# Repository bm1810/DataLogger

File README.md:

# DataLogger
Development files for DataLogger project

-- SCRIPTS --
Development scripts can be accessed in the scripts folder. These should be uploaded to the Arduino to which the datalogger shield is connected

-- EAGLE --
The Eagle folder holds the Eagle cad files and drawing files to route the boards on an S63 milling machine.

-- BOXCAD --

This folder holds the 3D printer STL files and Solidworks CAD files from creation of the box.

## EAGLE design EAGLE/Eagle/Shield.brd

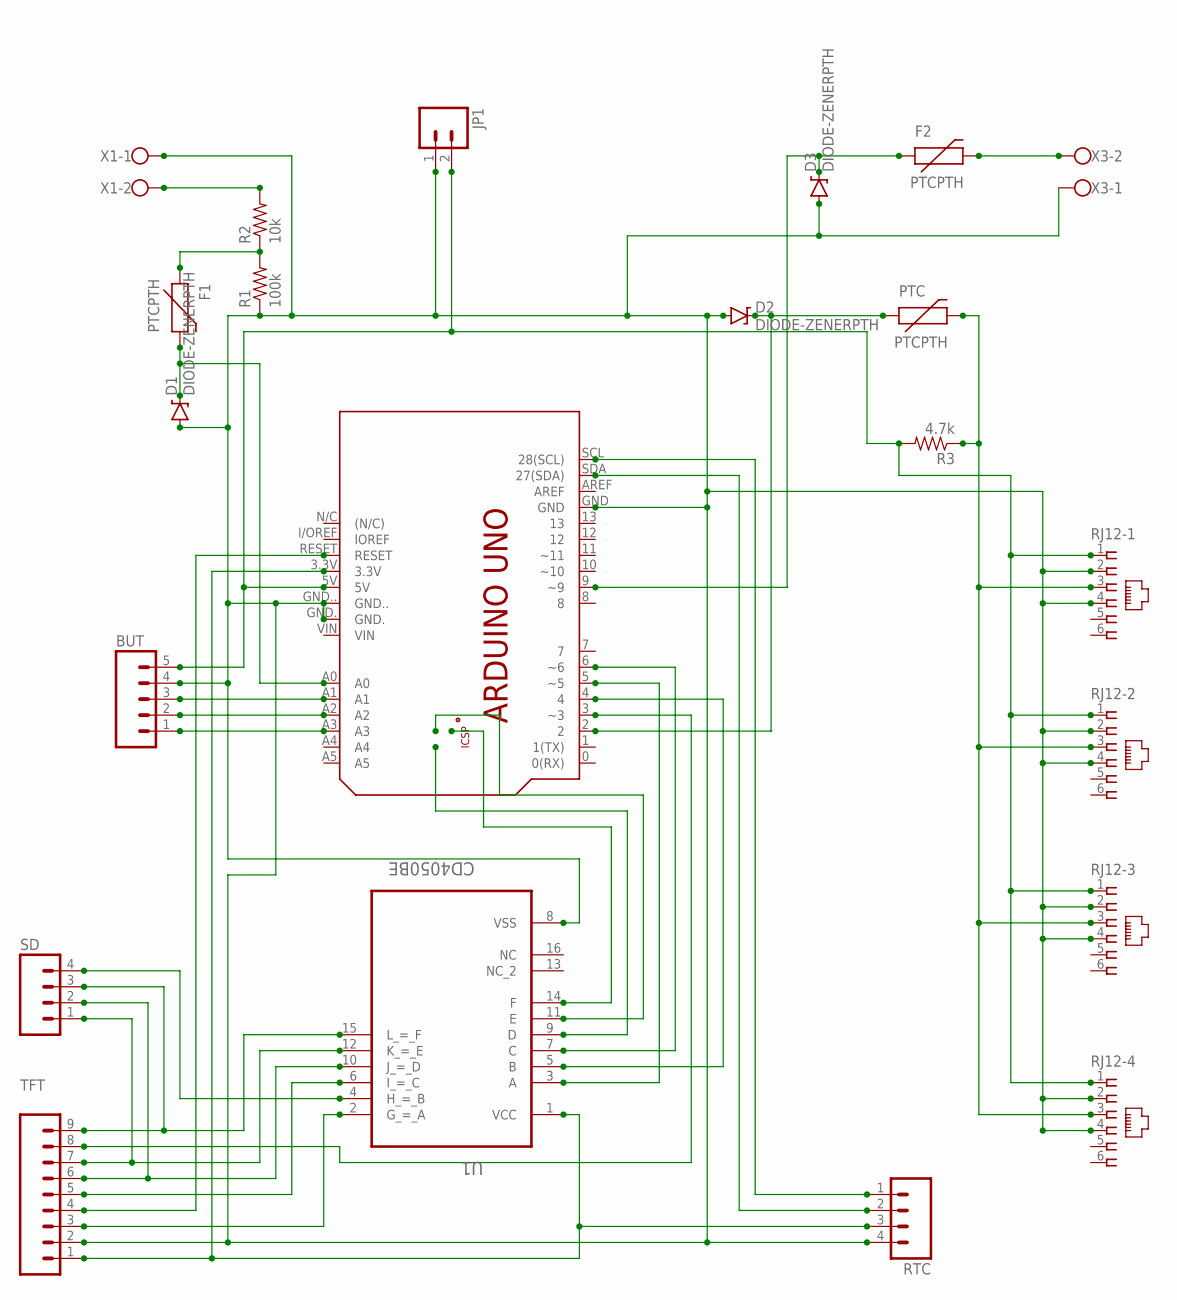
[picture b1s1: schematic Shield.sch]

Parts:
BUT: M05PTH_LONGPADS; 1X05_LONGPADS
D1, D2, D3: DIODE-ZENERPTH; DIODE-ZENER
F1, F2: PTCPTH; PTC
JP1: M023.5MM; SCREWTERMINAL-3.5MM-2
PCB1: ARDUINO_UNO
PTC: PTCPTH; PTC
R1: 100k; AXIAL-0.3
R2: 10k; AXIAL-0.3
R3: 4.7k; AXIAL-0.3
RJ12-1, RJ12-2, RJ12-3, RJ12-4: 555165-1
RTC: M04LONGPADS; 1X04_LONGPADS
SD: M04LONGPADS; 1X04_LONGPADS
TFT: M09LONGPADS; 1X09_LONGPADS
U1: CD4050BE; DIP254P762X508-16
X1, X3: W237-102

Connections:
GND: BUT.4, D1.P$2 (A), D2.P$2 (A), D3.P$2 (A), JP1.1, PCB1.GND, PCB1.GND., PCB1.GND.., R1.P$1 (1), RJ12-1.2, RJ12-1.4, RJ12-2.2, RJ12-2.4, RJ12-3.2, RJ12-3.4, RJ12-4.2, RJ12-4.4, RTC.4, TFT.2, U1.8 (VSS), X1.1, X3.1
unnamed: BUT.3, PCB1.A1
unnamed: PTC.P$2 (2), R3.P$1 (1), RJ12-1.3, RJ12-2.3, RJ12-3.3, RJ12-4.3
unnamed: PCB1.3.3V, RTC.3, TFT.1, U1.1 (VCC)
unnamed: D2.P$1 (C), PCB1.2, PTC.P$1 (1)
unnamed: PCB1.RESET, TFT.4
unnamed: SD.4, U1.4 (H_=_B)
unnamed: PCB1.5 (~5), U1.3 (A)
unnamed: PCB1.6 (~6), U1.7 (C)
unnamed: PCB1.MOSI, U1.9 (D)
unnamed: TFT.3, U1.2 (G_=_A)
unnamed: TFT.5, U1.6 (I_=_C)
unnamed: SD.2, TFT.6, U1.10 (J_=_D)
unnamed: PCB1.3 (~3), TFT.8
unnamed: SD.1, TFT.7, U1.12 (K_=_E)
unnamed: SD.3, TFT.9, U1.15 (L_=_F)
unnamed: PCB1.SCK, U1.11 (E)
unnamed: PCB1.MISO, U1.14 (F)
unnamed: BUT.5, JP1.2, PCB1.5V, R3.P$2 (2), RJ12-1.1, RJ12-2.1, RJ12-3.1, RJ12-4.1
unnamed: BUT.2, PCB1.A2
unnamed: PCB1.4, U1.5 (B)
unnamed: BUT.1, PCB1.A3
unnamed: PCB1.SDA (27(SDA)), RTC.2
unnamed: PCB1.SCL (28(SCL)), RTC.1
unnamed: F1.P$1 (1), R1.P$2 (2), R2.P$1 (1)
unnamed: D1.P$1 (C), F1.P$2 (2), PCB1.A0
unnamed: R2.P$2 (2), X1.2
unnamed: F2.P$2 (2), X3.2
unnamed: D3.P$1 (C), F2.P$1 (1), PCB1.9 (~9)

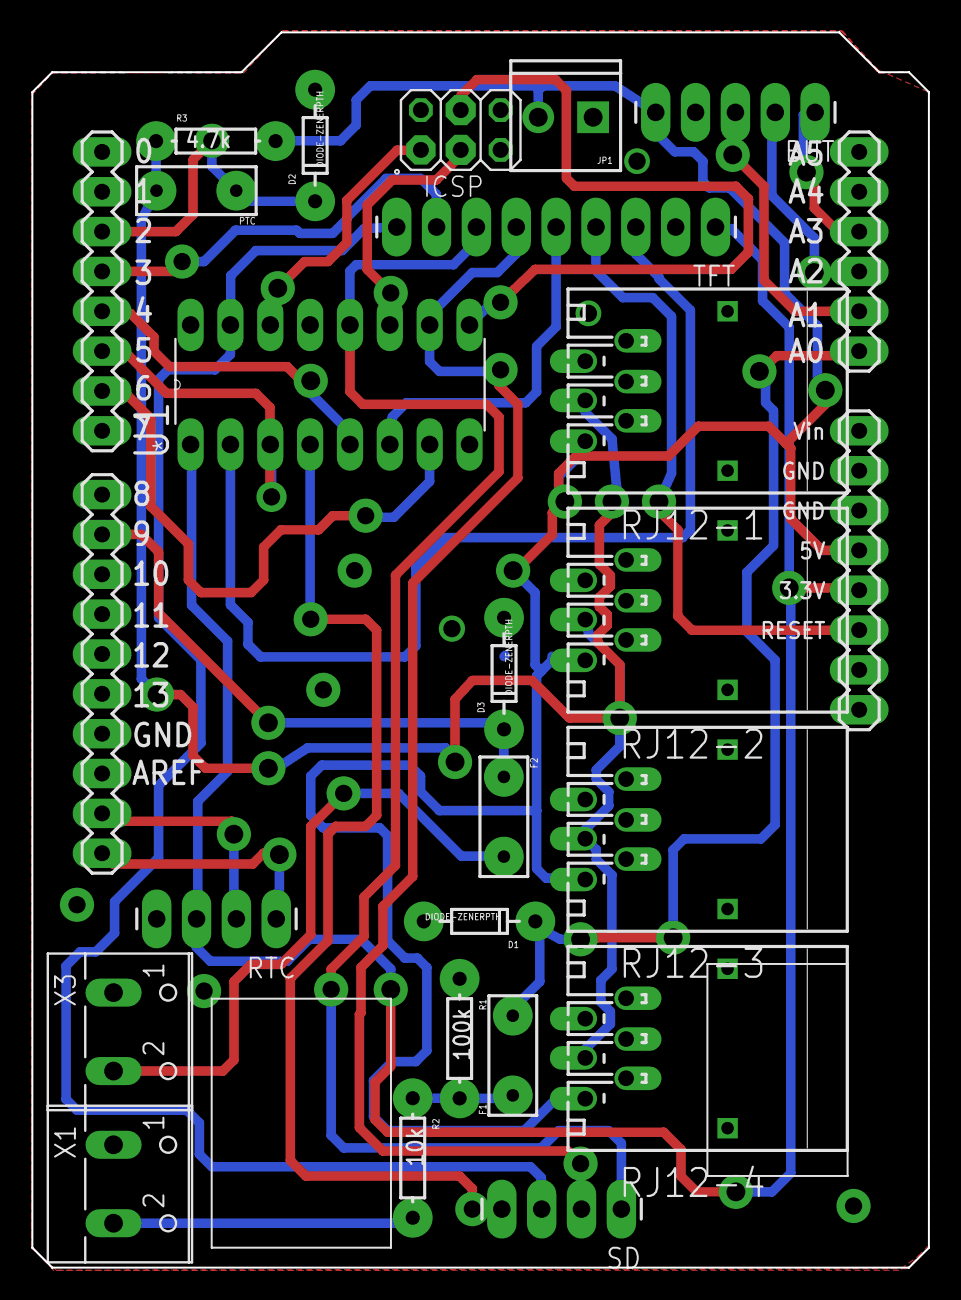
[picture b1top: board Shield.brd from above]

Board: 2 copper layers, 57.1 x 78.7 mm, 22 parts (0 on the bottom side), 29 nets.

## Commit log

2015-06-28 Changed folders, added eagle files, cad files and 3d printing files

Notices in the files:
parts and their libraries:
SparkFun-Connectors: Licensing: Creative Commons ShareAlike 4.0 International - https://creativecommons.org/licenses/by-sa/4.0
